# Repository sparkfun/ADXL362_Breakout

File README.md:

ADXL362 Breakout Board
======================

[
*ADXL362 Breakout (SEN-11446)*](https://www.sparkfun.com/products/11446)

The ADXL362 is a complete 3-axis MEMS acceleration measurement system that operates at extremely low power consumption levels.
It communicates over SPI, and can autonomously operate for "wake-on-shake" operation.

Repository Contents
-------------------
* **/Hardware** - All Eagle design files (.brd, .sch, .STL)
* **/Production** - Test bed files and production panel files

Available Libraries
-----------------------------
* [Winkel ICT ADXL362](https://github.com/winkelict/ADXL362)
* [Annem ADXL362](https://github.com/annem/ADXL362)

License Information
-------------------
The hardware is released under [Creative Commons ShareAlike 4.0 International](https://creativecommons.org/licenses/by-sa/4.0/).

Distributed as-is; no warranty is given.

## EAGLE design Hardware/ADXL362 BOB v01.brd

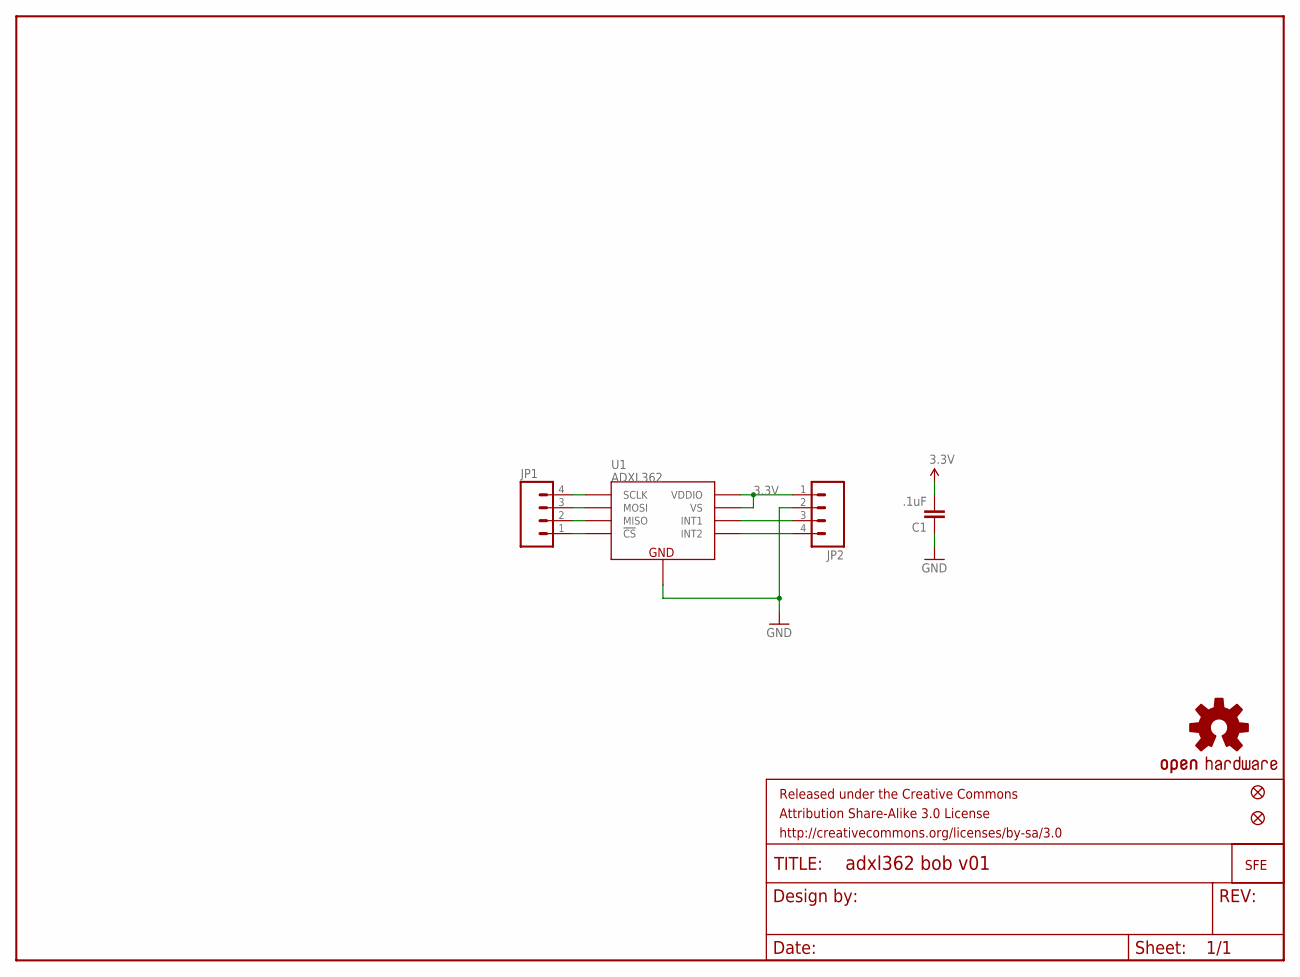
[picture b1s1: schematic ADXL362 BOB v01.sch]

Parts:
C1: .1uF; 0402-CAP
FRAME1: FRAME-LETTER; CREATIVE_COMMONS
JP1, JP2: M04PTH; 1X04
JP3: LOGO-SFESK; SFE-LOGO-FLAME
JP4, JP5: FIDUCIALUFIDUCIAL; MICRO-FIDUCIAL
U1: ADXL362
U$1: OSHW-LOGOS; OSHW-LOGO-S

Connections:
3.3V: C1.2, JP2.1, U1.P$1 (VDDIO), U1.P$14 (VS)
GND: C1.1, JP2.2, U1.P$12 (GND), U1.P$13 (GND), U1.P$16 (GND)
unnamed: JP1.4, U1.P$4 (SCLK)
unnamed: JP1.3, U1.P$6 (MOSI)
unnamed: JP1.2, U1.P$7 (MISO)
unnamed: JP1.1, U1.P$8 (!CS)
unnamed: JP2.3, U1.P$11 (INT1)
unnamed: JP2.4, U1.P$9 (INT2)

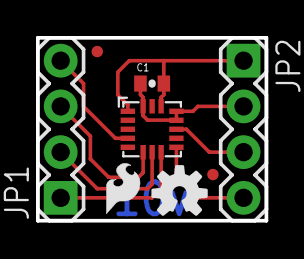
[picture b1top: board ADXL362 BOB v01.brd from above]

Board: 2 copper layers, 12.7 x 10.2 mm, 9 parts (0 on the bottom side), 8 nets.

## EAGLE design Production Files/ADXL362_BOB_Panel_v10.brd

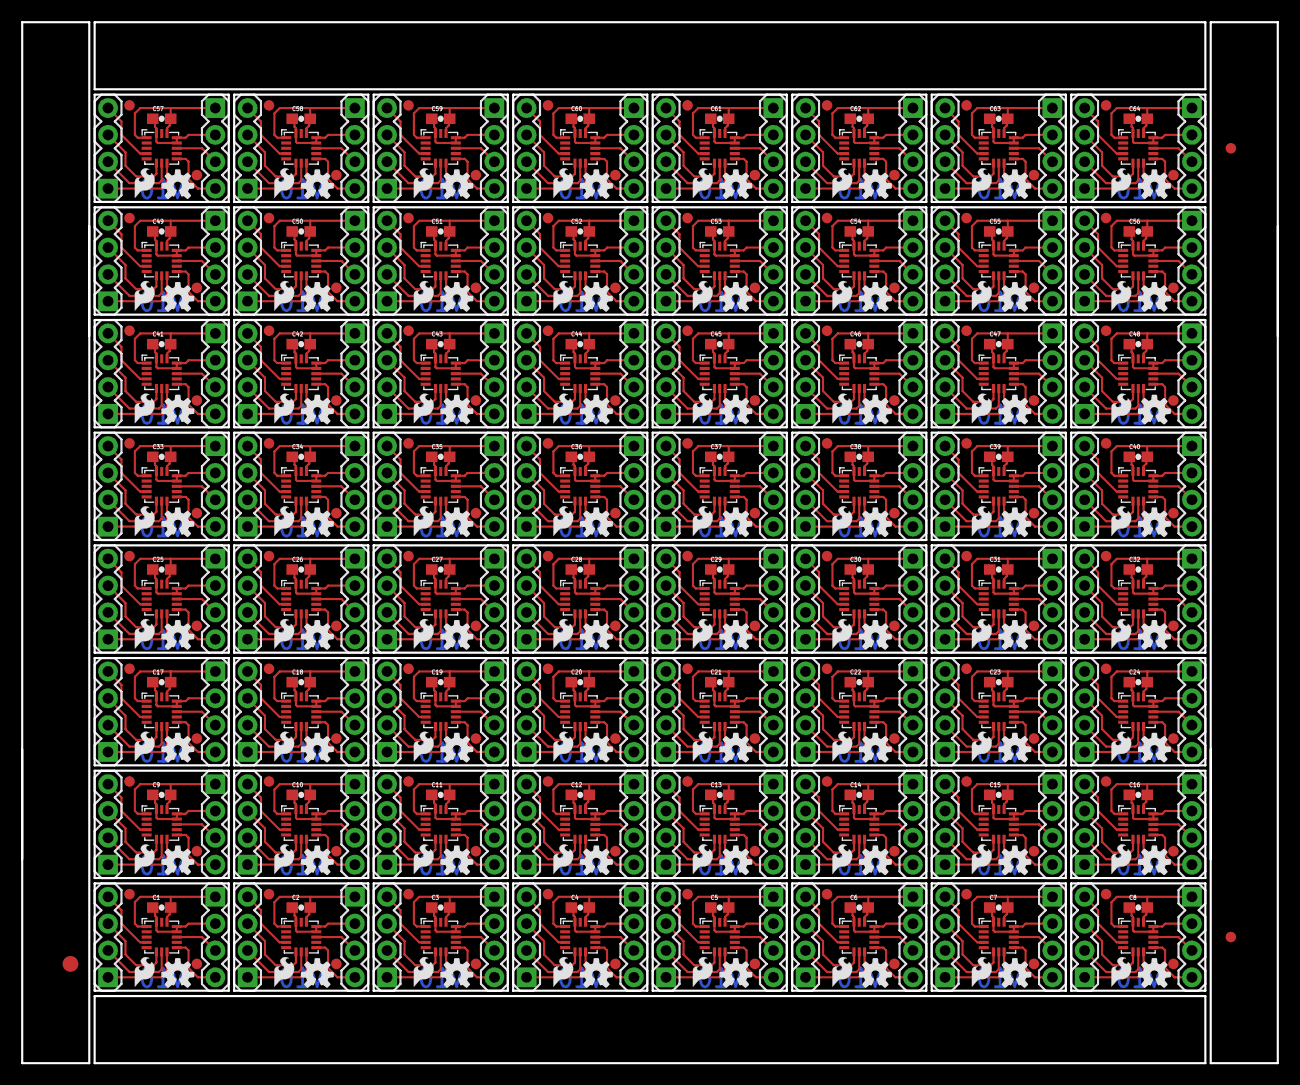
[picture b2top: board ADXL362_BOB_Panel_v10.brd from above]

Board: 2 copper layers, 118.9 x 98.6 mm, 515 parts (0 on the bottom side), 512 nets.

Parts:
C1, C2, C3, C4, C5, C6, C7, C8, C9, C10, C11, C12, C13, C14, C15, C16, C17, C18, C19, C20, C21, C22, C23, C24, C25, C26, C27, C28, C29, C30, C31, C32, C33, C34, C35, C36, C37, C38, C39, C40, C41, C42, C43, C44, C45, C46, C47, C48, C49, C50, C51, C52, C53, C54, C55, C56, C57, C58, C59, C60, C61, C62, C63, C64: .1uF; 0603-CAP
E$1: FIDUCIAL-1.5X3
E$4, E$5: FIDUCIAL-1X2
FID1, FID2, FID3, FID4, FID5, FID6, FID7, FID8, FID9, FID10, FID11, FID12, FID13, FID14, FID15, FID16, FID17, FID18, FID19, FID20, FID21, FID22, FID23, FID24, FID25, FID26, FID27, FID28, FID29, FID30, FID31, FID32, FID33, FID34, FID35, FID36, FID37, FID38, FID39, FID40, FID41, FID42, FID43, FID44, FID45, FID46, FID47, FID48, FID49, FID50, FID51, FID52, FID53, FID54, FID55, FID56, FID57, FID58, FID59, FID60, FID61, FID62, FID63, FID64, FID65, FID66, FID67, FID68, FID69, FID70, FID71, FID72, FID73, FID74, FID75, FID76, FID77, FID78, FID79, FID80, FID81, FID82, FID83, FID84, FID85, FID86, FID87, FID88, FID89, FID90, FID91, FID92, FID93, FID94, FID95, FID96, FID97, FID98, FID99, FID100, FID101, FID102, FID103, FID104, FID105, FID106, FID107, FID108, FID109, FID110, FID111, FID112, FID113, FID114, FID115, FID116, FID117, FID118, FID119, FID120, FID121, FID122, FID123, FID124, FID125, FID126, FID127, FID128: FIDUCIAL1X2; FIDUCIAL-1X2
JP1, JP2, JP4, JP5, JP7, JP8, JP10, JP11, JP13, JP14, JP16, JP17, JP19, JP20, JP22, JP23, JP25, JP26, JP28, JP29, JP31, JP32, JP34, JP35, JP37, JP38, JP40, JP41, JP43, JP44, JP46, JP47, JP49, JP50, JP52, JP53, JP55, JP56, JP58, JP59, JP61, JP62, JP64, JP65, JP67, JP68, JP70, JP71, JP73, JP74, JP76, JP77, JP79, JP80, JP82, JP83, JP85, JP86, JP88, JP89, JP91, JP92, JP94, JP95, JP97, JP98, JP100, JP101, JP103, JP104, JP106, JP107, JP109, JP110, JP112, JP113, JP115, JP116, JP118, JP119, JP121, JP122, JP124, JP125, JP127, JP128, JP130, JP131, JP133, JP134, JP136, JP137, JP139, JP140, JP142, JP143, JP145, JP146, JP148, JP149, JP151, JP152, JP154, JP155, JP157, JP158, JP160, JP161, JP163, JP164, JP166, JP167, JP169, JP170, JP172, JP173, JP175, JP176, JP178, JP179, JP181, JP182, JP184, JP185, JP187, JP188, JP190, JP191: 1X04
JP3, JP6, JP9, JP12, JP15, JP18, JP21, JP24, JP27, JP30, JP33, JP36, JP39, JP42, JP45, JP48, JP51, JP54, JP57, JP60, JP63, JP66, JP69, JP72, JP75, JP78, JP81, JP84, JP87, JP90, JP93, JP96, JP99, JP102, JP105, JP108, JP111, JP114, JP117, JP120, JP123, JP126, JP129, JP132, JP135, JP138, JP141, JP144, JP147, JP150, JP153, JP156, JP159, JP162, JP165, JP168, JP171, JP174, JP177, JP180, JP183, JP186, JP189, JP192: LOGO-SFESK; SFE-LOGO-FLAME
U1, U2, U3, U4, U5, U6, U7, U8, U9, U10, U11, U12, U13, U14, U15, U16, U17, U18, U19, U20, U21, U22, U23, U24, U25, U26, U27, U28, U29, U30, U31, U32, U33, U34, U35, U36, U37, U38, U39, U40, U41, U42, U43, U44, U45, U46, U47, U48, U49, U50, U51, U52, U53, U54, U55, U56, U57, U58, U59, U60, U61, U62, U63, U64: ADXL362-1:1
U$1, U$2, U$3, U$4, U$5, U$6, U$7, U$8, U$9, U$10, U$11, U$12, U$13, U$14, U$15, U$16, U$17, U$18, U$19, U$20, U$21, U$22, U$23, U$24, U$25, U$26, U$27, U$28, U$29, U$30, U$31, U$32, U$33, U$34, U$35, U$36, U$37, U$38, U$39, U$40, U$41, U$42, U$43, U$44, U$45, U$46, U$47, U$48, U$49, U$50, U$51, U$52, U$53, U$54, U$55, U$56, U$57, U$58, U$59, U$60, U$61, U$62, U$63, U$64: OSHW-LOGOS; OSHW-LOGO-S

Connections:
3.3V: C1.2, JP2.1, U1.P$1, U1.P$14
3.3V1: C2.2, JP5.1, U2.P$1, U2.P$14
3.3V2: C3.2, JP8.1, U3.P$1, U3.P$14
3.3V3: C4.2, JP11.1, U4.P$1, U4.P$14
3.3V4: C5.2, JP14.1, U5.P$1, U5.P$14
3.3V5: C6.2, JP17.1, U6.P$1, U6.P$14
3.3V6: C7.2, JP20.1, U7.P$1, U7.P$14
3.3V7: C8.2, JP23.1, U8.P$1, U8.P$14
3.3V8: C9.2, JP26.1, U9.P$1, U9.P$14
3.3V9: C10.2, JP29.1, U10.P$1, U10.P$14
3.3V10: C11.2, JP32.1, U11.P$1, U11.P$14
3.3V11: C12.2, JP35.1, U12.P$1, U12.P$14
3.3V12: C13.2, JP38.1, U13.P$1, U13.P$14
3.3V13: C14.2, JP41.1, U14.P$1, U14.P$14
3.3V14: C15.2, JP44.1, U15.P$1, U15.P$14
3.3V15: C16.2, JP47.1, U16.P$1, U16.P$14
3.3V16: C17.2, JP50.1, U17.P$1, U17.P$14
3.3V17: C18.2, JP53.1, U18.P$1, U18.P$14
3.3V18: C19.2, JP56.1, U19.P$1, U19.P$14
3.3V19: C20.2, JP59.1, U20.P$1, U20.P$14
3.3V20: C21.2, JP62.1, U21.P$1, U21.P$14
3.3V21: C22.2, JP65.1, U22.P$1, U22.P$14
3.3V22: C23.2, JP68.1, U23.P$1, U23.P$14
3.3V23: C24.2, JP71.1, U24.P$1, U24.P$14
3.3V24: C25.2, JP74.1, U25.P$1, U25.P$14
3.3V25: C26.2, JP77.1, U26.P$1, U26.P$14
3.3V26: C27.2, JP80.1, U27.P$1, U27.P$14
3.3V27: C28.2, JP83.1, U28.P$1, U28.P$14
3.3V28: C29.2, JP86.1, U29.P$1, U29.P$14
3.3V29: C30.2, JP89.1, U30.P$1, U30.P$14
3.3V30: C31.2, JP92.1, U31.P$1, U31.P$14
3.3V31: C32.2, JP95.1, U32.P$1, U32.P$14
3.3V32: C33.2, JP98.1, U33.P$1, U33.P$14
3.3V33: C34.2, JP101.1, U34.P$1, U34.P$14
3.3V34: C35.2, JP104.1, U35.P$1, U35.P$14
3.3V35: C36.2, JP107.1, U36.P$1, U36.P$14
3.3V36: C37.2, JP110.1, U37.P$1, U37.P$14
3.3V37: C38.2, JP113.1, U38.P$1, U38.P$14
3.3V38: C39.2, JP116.1, U39.P$1, U39.P$14
3.3V39: C40.2, JP119.1, U40.P$1, U40.P$14
3.3V40: C41.2, JP122.1, U41.P$1, U41.P$14
3.3V41: C42.2, JP125.1, U42.P$1, U42.P$14
3.3V42: C43.2, JP128.1, U43.P$1, U43.P$14
3.3V43: C44.2, JP131.1, U44.P$1, U44.P$14
3.3V44: C45.2, JP134.1, U45.P$1, U45.P$14
3.3V45: C46.2, JP137.1, U46.P$1, U46.P$14
3.3V46: C47.2, JP140.1, U47.P$1, U47.P$14
3.3V47: C48.2, JP143.1, U48.P$1, U48.P$14
3.3V48: C49.2, JP146.1, U49.P$1, U49.P$14
3.3V49: C50.2, JP149.1, U50.P$1, U50.P$14
3.3V50: C51.2, JP152.1, U51.P$1, U51.P$14
3.3V51: C52.2, JP155.1, U52.P$1, U52.P$14
3.3V52: C53.2, JP158.1, U53.P$1, U53.P$14
3.3V53: C54.2, JP161.1, U54.P$1, U54.P$14
3.3V54: C55.2, JP164.1, U55.P$1, U55.P$14
3.3V55: C56.2, JP167.1, U56.P$1, U56.P$14
3.3V56: C57.2, JP170.1, U57.P$1, U57.P$14
3.3V57: C58.2, JP173.1, U58.P$1, U58.P$14
3.3V58: C59.2, JP176.1, U59.P$1, U59.P$14
3.3V59: C60.2, JP179.1, U60.P$1, U60.P$14
3.3V60: C61.2, JP182.1, U61.P$1, U61.P$14
3.3V61: C62.2, JP185.1, U62.P$1, U62.P$14
3.3V62: C63.2, JP188.1, U63.P$1, U63.P$14
3.3V63: C64.2, JP191.1, U64.P$1, U64.P$14
GND: C1.1, JP2.2, U1.P$12, U1.P$13, U1.P$16
GND1: C2.1, JP5.2, U2.P$12, U2.P$13, U2.P$16
GND2: C3.1, JP8.2, U3.P$12, U3.P$13, U3.P$16
GND3: C4.1, JP11.2, U4.P$12, U4.P$13, U4.P$16
GND4: C5.1, JP14.2, U5.P$12, U5.P$13, U5.P$16
GND5: C6.1, JP17.2, U6.P$12, U6.P$13, U6.P$16
GND6: C7.1, JP20.2, U7.P$12, U7.P$13, U7.P$16
GND7: C8.1, JP23.2, U8.P$12, U8.P$13, U8.P$16
GND8: C9.1, JP26.2, U9.P$12, U9.P$13, U9.P$16
GND9: C10.1, JP29.2, U10.P$12, U10.P$13, U10.P$16
GND10: C11.1, JP32.2, U11.P$12, U11.P$13, U11.P$16
GND11: C12.1, JP35.2, U12.P$12, U12.P$13, U12.P$16
GND12: C13.1, JP38.2, U13.P$12, U13.P$13, U13.P$16
GND13: C14.1, JP41.2, U14.P$12, U14.P$13, U14.P$16
GND14: C15.1, JP44.2, U15.P$12, U15.P$13, U15.P$16
GND15: C16.1, JP47.2, U16.P$12, U16.P$13, U16.P$16
GND16: C17.1, JP50.2, U17.P$12, U17.P$13, U17.P$16
GND17: C18.1, JP53.2, U18.P$12, U18.P$13, U18.P$16
GND18: C19.1, JP56.2, U19.P$12, U19.P$13, U19.P$16
GND19: C20.1, JP59.2, U20.P$12, U20.P$13, U20.P$16
GND20: C21.1, JP62.2, U21.P$12, U21.P$13, U21.P$16
GND21: C22.1, JP65.2, U22.P$12, U22.P$13, U22.P$16
GND22: C23.1, JP68.2, U23.P$12, U23.P$13, U23.P$16
GND23: C24.1, JP71.2, U24.P$12, U24.P$13, U24.P$16
GND24: C25.1, JP74.2, U25.P$12, U25.P$13, U25.P$16
GND25: C26.1, JP77.2, U26.P$12, U26.P$13, U26.P$16
GND26: C27.1, JP80.2, U27.P$12, U27.P$13, U27.P$16
GND27: C28.1, JP83.2, U28.P$12, U28.P$13, U28.P$16
GND28: C29.1, JP86.2, U29.P$12, U29.P$13, U29.P$16
GND29: C30.1, JP89.2, U30.P$12, U30.P$13, U30.P$16
GND30: C31.1, JP92.2, U31.P$12, U31.P$13, U31.P$16
GND31: C32.1, JP95.2, U32.P$12, U32.P$13, U32.P$16
GND32: C33.1, JP98.2, U33.P$12, U33.P$13, U33.P$16
GND33: C34.1, JP101.2, U34.P$12, U34.P$13, U34.P$16
GND34: C35.1, JP104.2, U35.P$12, U35.P$13, U35.P$16
GND35: C36.1, JP107.2, U36.P$12, U36.P$13, U36.P$16
GND36: C37.1, JP110.2, U37.P$12, U37.P$13, U37.P$16
GND37: C38.1, JP113.2, U38.P$12, U38.P$13, U38.P$16
GND38: C39.1, JP116.2, U39.P$12, U39.P$13, U39.P$16
GND39: C40.1, JP119.2, U40.P$12, U40.P$13, U40.P$16
GND40: C41.1, JP122.2, U41.P$12, U41.P$13, U41.P$16
GND41: C42.1, JP125.2, U42.P$12, U42.P$13, U42.P$16
GND42: C43.1, JP128.2, U43.P$12, U43.P$13, U43.P$16
GND43: C44.1, JP131.2, U44.P$12, U44.P$13, U44.P$16
GND44: C45.1, JP134.2, U45.P$12, U45.P$13, U45.P$16
GND45: C46.1, JP137.2, U46.P$12, U46.P$13, U46.P$16
GND46: C47.1, JP140.2, U47.P$12, U47.P$13, U47.P$16
GND47: C48.1, JP143.2, U48.P$12, U48.P$13, U48.P$16
GND48: C49.1, JP146.2, U49.P$12, U49.P$13, U49.P$16
GND49: C50.1, JP149.2, U50.P$12, U50.P$13, U50.P$16
GND50: C51.1, JP152.2, U51.P$12, U51.P$13, U51.P$16
GND51: C52.1, JP155.2, U52.P$12, U52.P$13, U52.P$16
GND52: C53.1, JP158.2, U53.P$12, U53.P$13, U53.P$16
GND53: C54.1, JP161.2, U54.P$12, U54.P$13, U54.P$16
GND54: C55.1, JP164.2, U55.P$12, U55.P$13, U55.P$16
GND55: C56.1, JP167.2, U56.P$12, U56.P$13, U56.P$16
GND56: C57.1, JP170.2, U57.P$12, U57.P$13, U57.P$16
GND57: C58.1, JP173.2, U58.P$12, U58.P$13, U58.P$16
GND58: C59.1, JP176.2, U59.P$12, U59.P$13, U59.P$16
GND59: C60.1, JP179.2, U60.P$12, U60.P$13, U60.P$16
GND60: C61.1, JP182.2, U61.P$12, U61.P$13, U61.P$16
GND61: C62.1, JP185.2, U62.P$12, U62.P$13, U62.P$16
GND62: C63.1, JP188.2, U63.P$12, U63.P$13, U63.P$16
GND63: C64.1, JP191.2, U64.P$12, U64.P$13, U64.P$16
unnamed: JP1.4, U1.P$4
unnamed: JP1.3, U1.P$6
unnamed: JP1.2, U1.P$7
unnamed: JP1.1, U1.P$8
unnamed: JP4.4, U2.P$4
unnamed: JP4.3, U2.P$6
unnamed: JP2.3, U1.P$11
unnamed: JP2.4, U1.P$9
unnamed: JP4.2, U2.P$7
unnamed: JP4.1, U2.P$8
unnamed: JP5.3, U2.P$11
unnamed: JP5.4, U2.P$9
unnamed: JP7.4, U3.P$4
unnamed: JP7.3, U3.P$6
unnamed: JP7.2, U3.P$7
unnamed: JP7.1, U3.P$8
unnamed: JP8.3, U3.P$11
unnamed: JP8.4, U3.P$9
unnamed: JP10.4, U4.P$4
unnamed: JP10.3, U4.P$6
unnamed: JP10.2, U4.P$7
unnamed: JP10.1, U4.P$8
unnamed: JP11.3, U4.P$11
unnamed: JP11.4, U4.P$9
unnamed: JP13.4, U5.P$4
unnamed: JP13.3, U5.P$6
unnamed: JP13.2, U5.P$7
unnamed: JP13.1, U5.P$8
unnamed: JP14.3, U5.P$11
unnamed: JP14.4, U5.P$9
unnamed: JP16.4, U6.P$4
unnamed: JP16.3, U6.P$6
unnamed: JP16.2, U6.P$7
unnamed: JP16.1, U6.P$8
unnamed: JP17.3, U6.P$11
unnamed: JP17.4, U6.P$9
unnamed: JP19.4, U7.P$4
unnamed: JP19.3, U7.P$6
unnamed: JP19.2, U7.P$7
unnamed: JP19.1, U7.P$8
unnamed: JP20.3, U7.P$11
unnamed: JP20.4, U7.P$9
unnamed: JP22.4, U8.P$4
unnamed: JP22.3, U8.P$6
unnamed: JP22.2, U8.P$7
unnamed: JP22.1, U8.P$8
unnamed: JP23.3, U8.P$11
unnamed: JP23.4, U8.P$9
unnamed: JP25.4, U9.P$4
unnamed: JP25.3, U9.P$6
unnamed: JP25.2, U9.P$7
unnamed: JP25.1, U9.P$8
unnamed: JP26.3, U9.P$11
unnamed: JP26.4, U9.P$9
unnamed: JP28.4, U10.P$4
unnamed: JP28.3, U10.P$6
unnamed: JP28.2, U10.P$7
unnamed: JP28.1, U10.P$8
unnamed: JP29.3, U10.P$11
unnamed: JP29.4, U10.P$9
unnamed: JP31.4, U11.P$4
unnamed: JP31.3, U11.P$6
unnamed: JP31.2, U11.P$7
unnamed: JP31.1, U11.P$8
unnamed: JP32.3, U11.P$11
unnamed: JP32.4, U11.P$9
unnamed: JP34.4, U12.P$4
unnamed: JP34.3, U12.P$6
unnamed: JP34.2, U12.P$7
unnamed: JP34.1, U12.P$8
unnamed: JP35.3, U12.P$11
unnamed: JP35.4, U12.P$9
unnamed: JP37.4, U13.P$4
unnamed: JP37.3, U13.P$6
unnamed: JP37.2, U13.P$7
unnamed: JP37.1, U13.P$8
unnamed: JP38.3, U13.P$11
unnamed: JP38.4, U13.P$9
unnamed: JP40.4, U14.P$4
unnamed: JP40.3, U14.P$6
unnamed: JP40.2, U14.P$7
unnamed: JP40.1, U14.P$8
unnamed: JP41.3, U14.P$11
unnamed: JP41.4, U14.P$9
unnamed: JP43.4, U15.P$4
unnamed: JP43.3, U15.P$6
unnamed: JP43.2, U15.P$7
unnamed: JP43.1, U15.P$8
unnamed: JP44.3, U15.P$11
unnamed: JP44.4, U15.P$9
unnamed: JP46.4, U16.P$4
unnamed: JP46.3, U16.P$6
unnamed: JP46.2, U16.P$7
unnamed: JP46.1, U16.P$8
unnamed: JP47.3, U16.P$11
unnamed: JP47.4, U16.P$9
unnamed: JP49.4, U17.P$4
unnamed: JP49.3, U17.P$6
unnamed: JP49.2, U17.P$7
unnamed: JP49.1, U17.P$8
unnamed: JP50.3, U17.P$11
unnamed: JP50.4, U17.P$9
unnamed: JP52.4, U18.P$4
unnamed: JP52.3, U18.P$6
unnamed: JP52.2, U18.P$7
unnamed: JP52.1, U18.P$8
unnamed: JP53.3, U18.P$11
unnamed: JP53.4, U18.P$9
unnamed: JP55.4, U19.P$4
unnamed: JP55.3, U19.P$6
unnamed: JP55.2, U19.P$7
unnamed: JP55.1, U19.P$8
unnamed: JP56.3, U19.P$11
unnamed: JP56.4, U19.P$9
unnamed: JP58.4, U20.P$4
unnamed: JP58.3, U20.P$6
unnamed: JP58.2, U20.P$7
unnamed: JP58.1, U20.P$8
unnamed: JP59.3, U20.P$11
unnamed: JP59.4, U20.P$9
unnamed: JP61.4, U21.P$4
unnamed: JP61.3, U21.P$6
unnamed: JP61.2, U21.P$7
unnamed: JP61.1, U21.P$8
unnamed: JP62.3, U21.P$11
unnamed: JP62.4, U21.P$9
unnamed: JP64.4, U22.P$4
unnamed: JP64.3, U22.P$6
unnamed: JP64.2, U22.P$7
unnamed: JP64.1, U22.P$8
unnamed: JP65.3, U22.P$11
unnamed: JP65.4, U22.P$9
unnamed: JP67.4, U23.P$4
unnamed: JP67.3, U23.P$6
unnamed: JP67.2, U23.P$7
unnamed: JP67.1, U23.P$8
unnamed: JP68.3, U23.P$11
unnamed: JP68.4, U23.P$9
unnamed: JP70.4, U24.P$4
unnamed: JP70.3, U24.P$6
unnamed: JP70.2, U24.P$7
unnamed: JP70.1, U24.P$8
unnamed: JP71.3, U24.P$11
unnamed: JP71.4, U24.P$9
unnamed: JP73.4, U25.P$4
unnamed: JP73.3, U25.P$6
unnamed: JP73.2, U25.P$7
unnamed: JP73.1, U25.P$8
unnamed: JP74.3, U25.P$11
unnamed: JP74.4, U25.P$9
unnamed: JP76.4, U26.P$4
unnamed: JP76.3, U26.P$6
unnamed: JP76.2, U26.P$7
unnamed: JP76.1, U26.P$8
unnamed: JP77.3, U26.P$11
unnamed: JP77.4, U26.P$9
unnamed: JP79.4, U27.P$4
unnamed: JP79.3, U27.P$6
unnamed: JP79.2, U27.P$7
unnamed: JP79.1, U27.P$8
unnamed: JP80.3, U27.P$11
unnamed: JP80.4, U27.P$9
unnamed: JP82.4, U28.P$4
unnamed: JP82.3, U28.P$6
unnamed: JP82.2, U28.P$7
unnamed: JP82.1, U28.P$8
unnamed: JP83.3, U28.P$11
unnamed: JP83.4, U28.P$9
unnamed: JP85.4, U29.P$4
unnamed: JP85.3, U29.P$6
unnamed: JP85.2, U29.P$7
unnamed: JP85.1, U29.P$8
unnamed: JP86.3, U29.P$11
unnamed: JP86.4, U29.P$9
unnamed: JP88.4, U30.P$4
unnamed: JP88.3, U30.P$6
unnamed: JP88.2, U30.P$7
unnamed: JP88.1, U30.P$8
unnamed: JP89.3, U30.P$11
unnamed: JP89.4, U30.P$9
unnamed: JP91.4, U31.P$4
unnamed: JP91.3, U31.P$6
unnamed: JP91.2, U31.P$7
unnamed: JP91.1, U31.P$8
unnamed: JP92.3, U31.P$11
unnamed: JP92.4, U31.P$9
unnamed: JP94.4, U32.P$4
unnamed: JP94.3, U32.P$6
unnamed: JP94.2, U32.P$7
unnamed: JP94.1, U32.P$8
unnamed: JP95.3, U32.P$11
unnamed: JP95.4, U32.P$9
unnamed: JP97.4, U33.P$4
unnamed: JP97.3, U33.P$6
unnamed: JP97.2, U33.P$7
unnamed: JP97.1, U33.P$8
unnamed: JP98.3, U33.P$11
unnamed: JP98.4, U33.P$9
unnamed: JP100.4, U34.P$4
unnamed: JP100.3, U34.P$6
unnamed: JP100.2, U34.P$7
unnamed: JP100.1, U34.P$8
unnamed: JP101.3, U34.P$11
unnamed: JP101.4, U34.P$9
unnamed: JP103.4, U35.P$4
unnamed: JP103.3, U35.P$6
unnamed: JP103.2, U35.P$7
unnamed: JP103.1, U35.P$8
unnamed: JP104.3, U35.P$11
unnamed: JP104.4, U35.P$9
unnamed: JP106.4, U36.P$4
unnamed: JP106.3, U36.P$6
unnamed: JP106.2, U36.P$7
unnamed: JP106.1, U36.P$8
unnamed: JP107.3, U36.P$11
unnamed: JP107.4, U36.P$9
unnamed: JP109.4, U37.P$4
unnamed: JP109.3, U37.P$6
unnamed: JP109.2, U37.P$7
unnamed: JP109.1, U37.P$8
unnamed: JP110.3, U37.P$11
unnamed: JP110.4, U37.P$9
unnamed: JP112.4, U38.P$4
unnamed: JP112.3, U38.P$6
unnamed: JP112.2, U38.P$7
unnamed: JP112.1, U38.P$8
unnamed: JP113.3, U38.P$11
unnamed: JP113.4, U38.P$9
unnamed: JP115.4, U39.P$4
unnamed: JP115.3, U39.P$6
unnamed: JP115.2, U39.P$7
unnamed: JP115.1, U39.P$8
unnamed: JP116.3, U39.P$11
unnamed: JP116.4, U39.P$9
unnamed: JP118.4, U40.P$4
unnamed: JP118.3, U40.P$6
unnamed: JP118.2, U40.P$7
unnamed: JP118.1, U40.P$8
unnamed: JP119.3, U40.P$11
unnamed: JP119.4, U40.P$9
unnamed: JP121.4, U41.P$4
unnamed: JP121.3, U41.P$6
unnamed: JP121.2, U41.P$7
unnamed: JP121.1, U41.P$8
unnamed: JP122.3, U41.P$11
unnamed: JP122.4, U41.P$9
unnamed: JP124.4, U42.P$4
unnamed: JP124.3, U42.P$6
unnamed: JP124.2, U42.P$7
unnamed: JP124.1, U42.P$8
unnamed: JP125.3, U42.P$11
unnamed: JP125.4, U42.P$9
unnamed: JP127.4, U43.P$4
unnamed: JP127.3, U43.P$6
unnamed: JP127.2, U43.P$7
unnamed: JP127.1, U43.P$8
unnamed: JP128.3, U43.P$11
unnamed: JP128.4, U43.P$9
unnamed: JP130.4, U44.P$4
unnamed: JP130.3, U44.P$6
unnamed: JP130.2, U44.P$7
unnamed: JP130.1, U44.P$8
unnamed: JP131.3, U44.P$11
unnamed: JP131.4, U44.P$9
unnamed: JP133.4, U45.P$4
unnamed: JP133.3, U45.P$6
unnamed: JP133.2, U45.P$7
unnamed: JP133.1, U45.P$8
unnamed: JP134.3, U45.P$11
unnamed: JP134.4, U45.P$9
unnamed: JP136.4, U46.P$4
unnamed: JP136.3, U46.P$6
unnamed: JP136.2, U46.P$7
unnamed: JP136.1, U46.P$8
unnamed: JP137.3, U46.P$11
unnamed: JP137.4, U46.P$9
unnamed: JP139.4, U47.P$4
unnamed: JP139.3, U47.P$6
unnamed: JP139.2, U47.P$7
unnamed: JP139.1, U47.P$8
unnamed: JP140.3, U47.P$11
unnamed: JP140.4, U47.P$9
unnamed: JP142.4, U48.P$4
unnamed: JP142.3, U48.P$6
unnamed: JP142.2, U48.P$7
unnamed: JP142.1, U48.P$8
unnamed: JP143.3, U48.P$11
unnamed: JP143.4, U48.P$9
unnamed: JP145.4, U49.P$4
unnamed: JP145.3, U49.P$6
unnamed: JP145.2, U49.P$7
unnamed: JP145.1, U49.P$8
unnamed: JP146.3, U49.P$11
unnamed: JP146.4, U49.P$9
unnamed: JP148.4, U50.P$4
unnamed: JP148.3, U50.P$6
unnamed: JP148.2, U50.P$7
unnamed: JP148.1, U50.P$8
unnamed: JP149.3, U50.P$11
unnamed: JP149.4, U50.P$9
unnamed: JP151.4, U51.P$4
unnamed: JP151.3, U51.P$6
unnamed: JP151.2, U51.P$7
unnamed: JP151.1, U51.P$8
unnamed: JP152.3, U51.P$11
unnamed: JP152.4, U51.P$9
unnamed: JP154.4, U52.P$4
unnamed: JP154.3, U52.P$6
unnamed: JP154.2, U52.P$7
unnamed: JP154.1, U52.P$8
unnamed: JP155.3, U52.P$11
unnamed: JP155.4, U52.P$9
unnamed: JP157.4, U53.P$4
unnamed: JP157.3, U53.P$6
unnamed: JP157.2, U53.P$7
unnamed: JP157.1, U53.P$8
unnamed: JP158.3, U53.P$11
unnamed: JP158.4, U53.P$9
unnamed: JP160.4, U54.P$4
unnamed: JP160.3, U54.P$6
unnamed: JP160.2, U54.P$7
unnamed: JP160.1, U54.P$8
unnamed: JP161.3, U54.P$11
unnamed: JP161.4, U54.P$9
unnamed: JP163.4, U55.P$4
unnamed: JP163.3, U55.P$6
unnamed: JP163.2, U55.P$7
unnamed: JP163.1, U55.P$8
unnamed: JP164.3, U55.P$11
unnamed: JP164.4, U55.P$9
unnamed: JP166.4, U56.P$4
unnamed: JP166.3, U56.P$6
unnamed: JP166.2, U56.P$7
unnamed: JP166.1, U56.P$8
unnamed: JP167.3, U56.P$11
unnamed: JP167.4, U56.P$9
unnamed: JP169.4, U57.P$4
unnamed: JP169.3, U57.P$6
unnamed: JP169.2, U57.P$7
unnamed: JP169.1, U57.P$8
unnamed: JP170.3, U57.P$11
unnamed: JP170.4, U57.P$9
unnamed: JP172.4, U58.P$4
unnamed: JP172.3, U58.P$6
unnamed: JP172.2, U58.P$7
unnamed: JP172.1, U58.P$8
unnamed: JP173.3, U58.P$11
unnamed: JP173.4, U58.P$9
unnamed: JP175.4, U59.P$4
unnamed: JP175.3, U59.P$6
unnamed: JP175.2, U59.P$7
unnamed: JP175.1, U59.P$8
unnamed: JP176.3, U59.P$11
unnamed: JP176.4, U59.P$9
unnamed: JP178.4, U60.P$4
unnamed: JP178.3, U60.P$6
unnamed: JP178.2, U60.P$7
unnamed: JP178.1, U60.P$8
unnamed: JP179.3, U60.P$11
unnamed: JP179.4, U60.P$9
unnamed: JP181.4, U61.P$4
unnamed: JP181.3, U61.P$6
unnamed: JP181.2, U61.P$7
unnamed: JP181.1, U61.P$8
unnamed: JP182.3, U61.P$11
unnamed: JP182.4, U61.P$9
unnamed: JP184.4, U62.P$4
unnamed: JP184.3, U62.P$6
unnamed: JP184.2, U62.P$7
unnamed: JP184.1, U62.P$8
unnamed: JP185.3, U62.P$11
unnamed: JP185.4, U62.P$9
unnamed: JP187.4, U63.P$4
unnamed: JP187.3, U63.P$6
unnamed: JP187.2, U63.P$7
unnamed: JP187.1, U63.P$8
unnamed: JP188.3, U63.P$11
unnamed: JP188.4, U63.P$9
unnamed: JP190.4, U64.P$4
unnamed: JP190.3, U64.P$6
unnamed: JP190.2, U64.P$7
unnamed: JP190.1, U64.P$8
unnamed: JP191.3, U64.P$11
unnamed: JP191.4, U64.P$9

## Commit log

2013-09-23 Initial Commit
    With Readme gitignore and eagle files
2014-01-23 Moved to 0603, Traces, 1:1
    1:1 on the Adxl362
    Minor trace re-route
    cap moved to 0603
    Sch update
    Rev #1 update
2014-02-11 changed fiducials from micro to regular
2014-02-11 created panel v10
2014-08-07 Adding part info to README, adding current files to repo
2014-08-07 Adding back in rev files
2022-01-29 Update README.md
    As proposed by Russell Turner from Sparkfun <techsupport@sparkfun.com> through email:
    Awesome! The way we can get it onto our site/page is to run over to https://github.com/sparkfun/ADXL362_Breakout/issues and make a merge request for your library and one of our engineers will get it 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

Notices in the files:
parts and their libraries:
SparkFun-Sensors: Licensing: CC v3.0 Share-Alike You are welcome to use this library for commercial purposes.
SparkFun-Aesthetics: Released under the Creative Commons Attribution Share-Alike 3.0 License
SparkFun-Aesthetics: http://creativecommons.org/licenses/by-sa/3.0
